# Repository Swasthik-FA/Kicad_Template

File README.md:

<!--PCB_BLOCK-->
<table align="center">
  <tr>
    <td align="center">
      
      <br><sub><b>Front</b></sub>
    </td>
    <td align="center">
      
      <br><sub><b>Back</b></sub>
    </td>
  </tr>
</table>

***

## SPECIFICATIONS

| Parameter | Value |
| --- | --- |
| Dimensions | 125.74 x 53.08 mm |
<!--/PCB_BLOCK-->

***

## DIRECTORY STRUCTURE

    .
    ├─ .github/workflows  # CI pipeline (feature push, PR gates, release)
    ├─ HTML               # Generated reports / Pages site (CI output)
    ├─ config             # KiBot YAML configs and report templates
    │  ├─ kibot           # Orchestrator + per-output YAMLs
    │  └─ web             # Themed CSS for generated HTML
    ├─ docs               # Project images and documentation assets
    ├─ hardware           # KiCad project (source of truth)
    ├─ manufacturing      # Auto-generated fabrication artifacts
    └─ scripts            # Helper scripts (rename project)

<h1 align="center"><!--REPO_NAME-->Kicad_Template<!--/REPO_NAME--></h1>

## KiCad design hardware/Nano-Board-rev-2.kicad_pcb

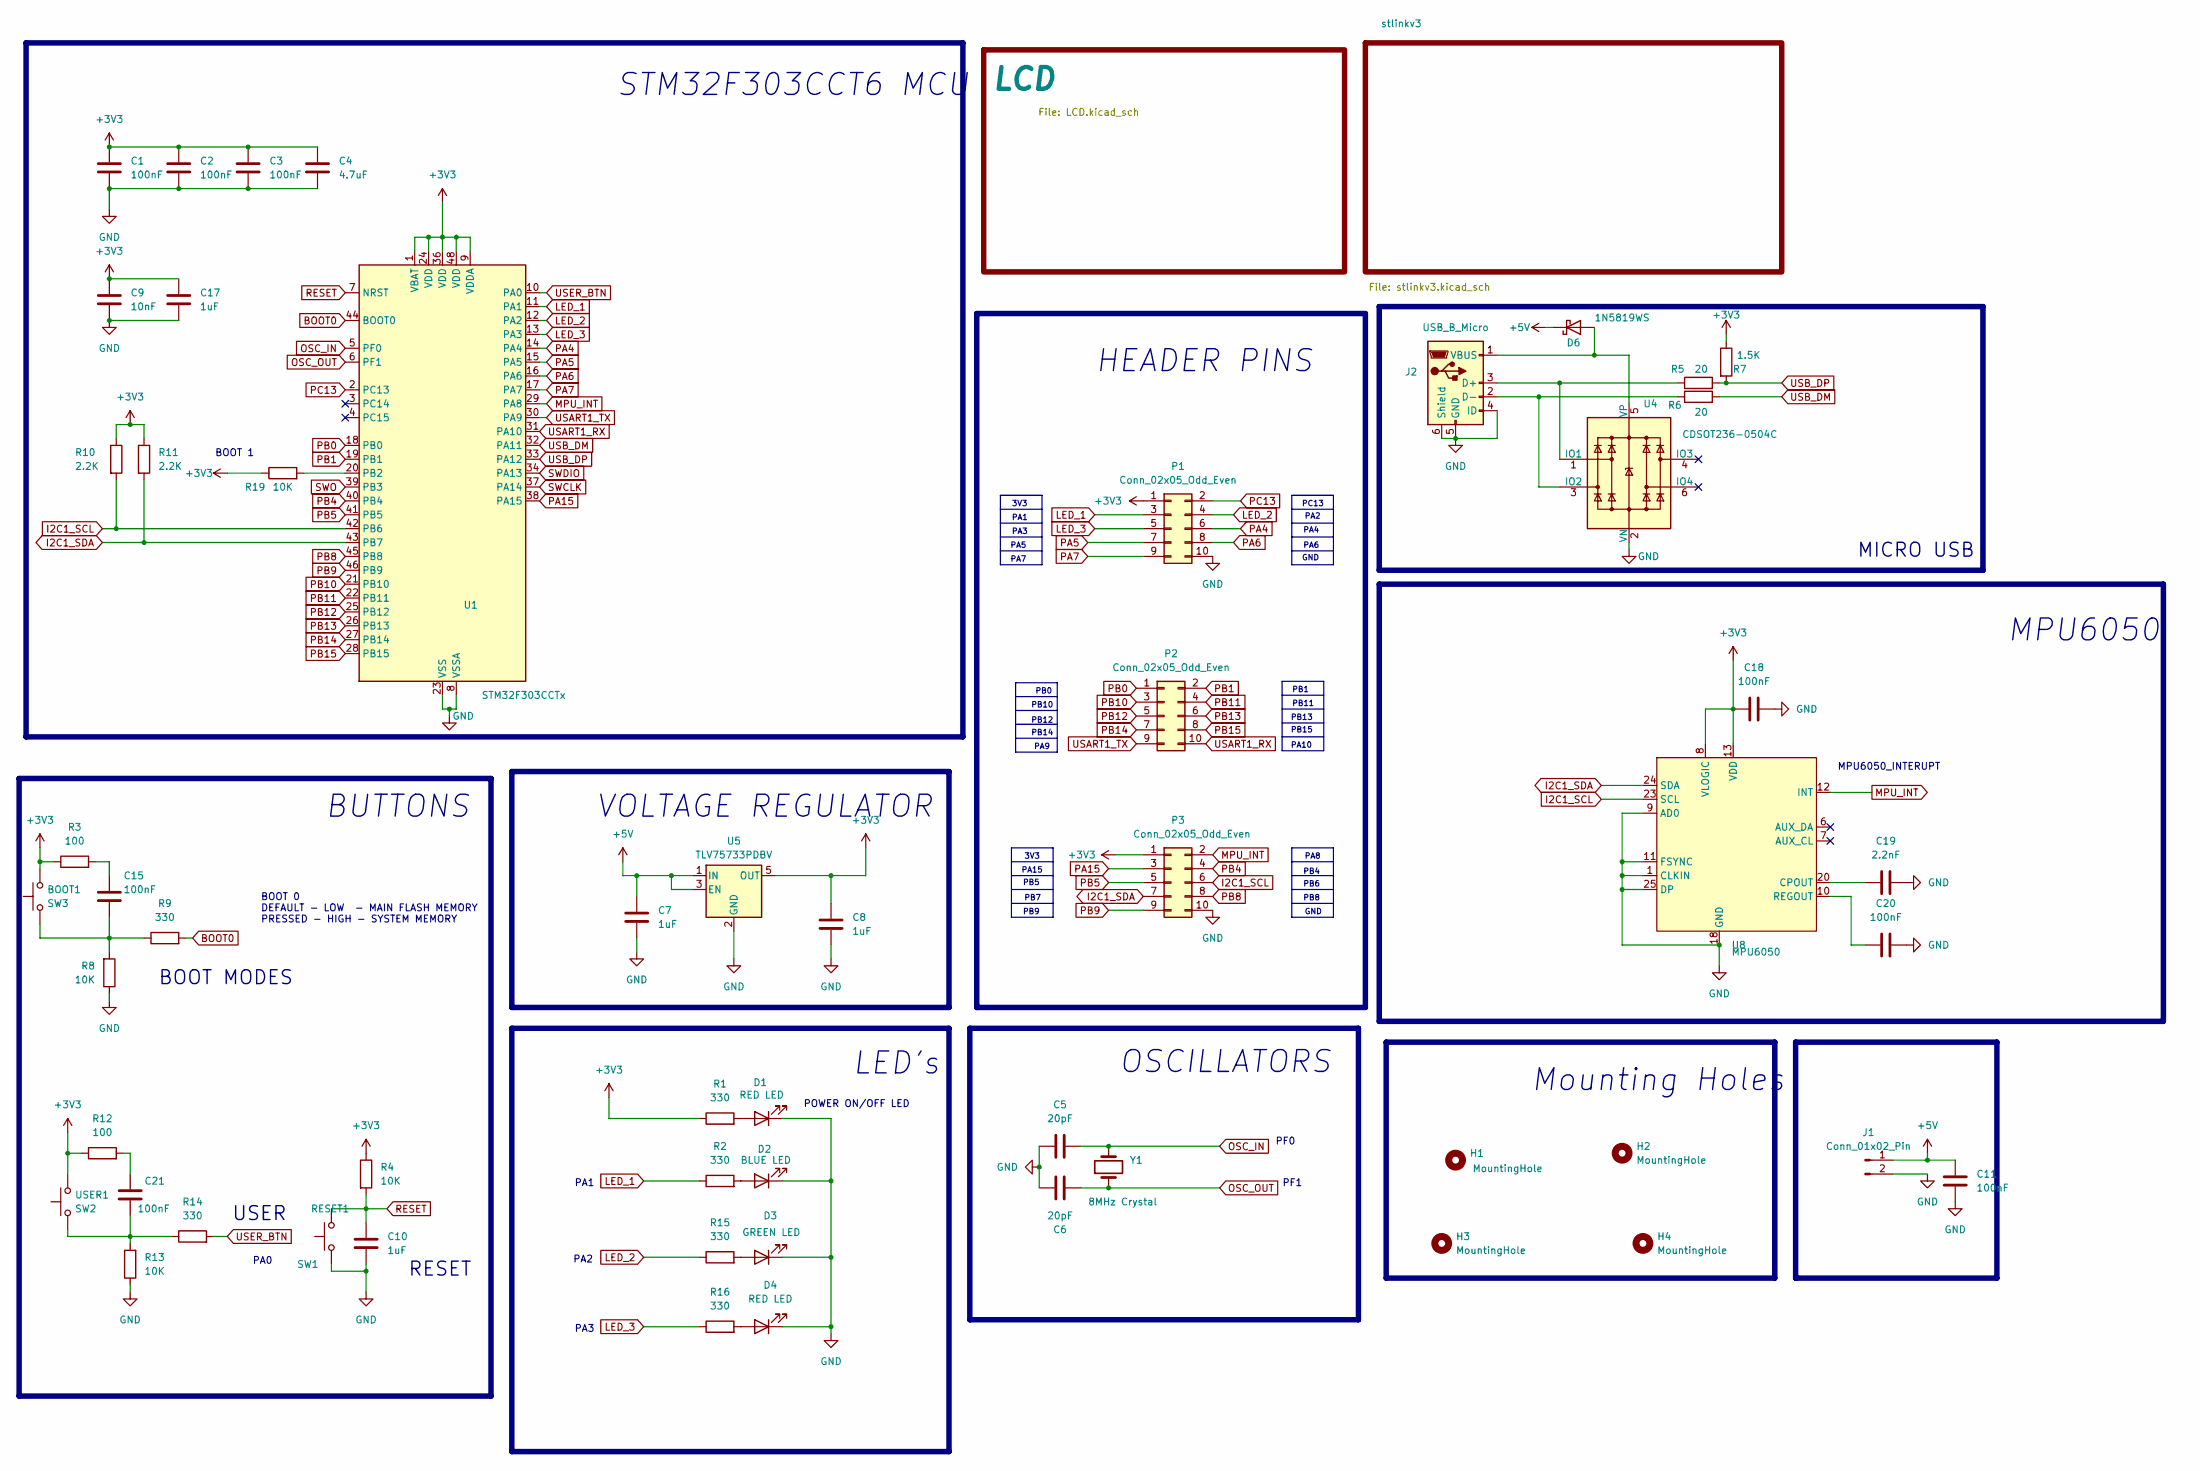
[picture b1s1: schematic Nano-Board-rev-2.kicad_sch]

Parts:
BOOT1: SW3; SW_Tactile_SPST_NO_Straight_CK_PTS636Sx25SMTRLFS; MPN TS1101-C-W; LCSC C318938
C1, C2, C3, C15, C18, C20, C21: 100nF; C_0402_1005Metric; MPN TCC0402X5R1 04Z160A; LCSC C48579247
C4: 4.7uF; C_0402_1005Metric; MPN TCC0402X5R4 75M6R3AT; LCSC C48579247
C5, C6: 20pF; C_0402_1005Metric; MPN 0402CG200J50 0NT; LCSC C1554
C7, C8: 1uF; C_0402_1005Metric; LCSC C7503519
C9: 10nF; C_0402_1005Metric; MPN CC0402KRX7R9BB; LCSC C60133
C10, C17: 1uF; C_0402_1005Metric; MPN CL05A105KP5NNNC; LCSC C7503519
C11: 100nF; C_0402_1005Metric
C19: 2.2nF; C_0402_1005Metric; MPN 0402B222K500CT; LCSC C338130
D1, D4: RED LED; LED_0603_1608Metric; MPN BLHUB37A-AV-TRB; LCSC C165980
D2: BLUE LED; LED_0603_1608Metric; MPN BLHB337A-AV-TRB; LCSC C165977
D3: GREEN LED; LED_0603_1608Metric; MPN SZYY0402YG; LCSC C434449
D6: 1N5819WS; D_SOD-123; LCSC C191023
H1, H2, H3, H4: MountingHole; MountingHole_2.2mm_M2
J1: Conn_01x02_Pin; PinSocket_1x02_P2.54mm_Vertical
J2: USB_B_Micro; micro_USB; MPN KH2.54FH1X12P-H8.5; LCSC C25503144
P1, P2, P3: Conn_02x05_Odd_Even; PinSocket_2x05_P2.54mm_Vertical_SMD; MPN 2.54-2*5P; LCSC C843271
R1, R2, R9, R14, R15, R16: 330; R_0402_1005Metric; MPN FRC0402J331 TS; LCSC C2906929
R3, R12: 100; R_0402_1005Metric; MPN SCR0402J100R; LCSC C3017466
R4: 10K; R_0402_1005Metric; MPN SCR0402J100K; LCSC C51035904
R5, R6: 20; R_0402_1005Metric; MPN RC0402FR-0720RL; LCSC C138031
R7: 1.5K; R_0402_1005Metric; MPN FRC0402J152TS; LCSC C2929900
R8, R13, R19: 10K; R_0402_1005Metric; MPN SCR0402F10K; LCSC C51035904
R10, R11: 2.2K; R_0402_1005Metric; MPN CR0402FF2201G; LCSC C100309
RESET1: SW1; SW_Tactile_SPST_NO_Straight_CK_PTS636Sx25SMTRLFS; MPN TS1101-C-W; LCSC C318938
U1: STM32F303CCTx; LQFP-48_7x7mm_P0.5mm; MPN STM32F303CC T6; LCSC C81523
U4: CDSOT236-0504C; SOT-23-6; MPN CDSOT236- 0504C; LCSC C41409337
U5: TLV75733PDBV; SOT-23-5; LCSC C485517
U8: MPU6050; Mpu6050; MPN MPU-6050
USER1: SW2; SW_Tactile_SPST_NO_Straight_CK_PTS636Sx25SMTRLFS; MPN TS1101-C-W; LCSC C318938
Y1: 8MHz Crystal; Crystal_SMD_HC49-SD; MPN X49SM8MSD2; LCSC C12674

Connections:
+3V3: BOOT1.2, C1.1, C2.1, C3.1, C4.1, C8.1, C9.1, C17.1, C18.1, P1.1, P3.1, R1.1, R3.1, R4.1, R7.1, R10.1, R11.1, R12.1, R19.1, U1.1 (VBAT), U1.9 (VDDA), U1.24 (VDD), U1.36 (VDD), U1.48 (VDD), U5.5 (OUT), U8.8 (VLOGIC), U8.13 (VDD), USER1.2; also elsewhere on the board
+5V: C7.1, C11.1, D6.1 (K), J1.1, U5.1 (IN), U5.3 (EN); also elsewhere on the board
BOOT0: R9.2, U1.44 (BOOT0)
GND: C1.2, C2.2, C3.2, C4.2, C5.1, C6.1, C7.2, C8.2, C9.2, C10.2, C11.2, C17.2, C18.2, C19.2, C20.2, D1.1 (K), D2.1 (K), D3.1 (K), D4.1 (K), J1.2, J2.4 (ID), J2.5 (GND), J2.6 (Shield), P1.10, P3.10, R8.1, R13.1, RESET1.1, U1.8 (VSSA), U1.23 (VSS), U1.35 (VSS), U1.47 (VSS), U4.2 (VN), U5.2 (GND), U8.1 (CLKIN), U8.9 (AD0), U8.11 (FSYNC), U8.18 (GND), U8.25 (DP); also elsewhere on the board
I2C1_SCL: P3.6, R10.2, U1.42 (PB6), U8.23 (SCL)
I2C1_SDA: P3.7, R11.2, U1.43 (PB7), U8.24 (SDA)
LED_1: P1.3, R2.1, U1.11 (PA1)
LED_2: P1.4, R15.1, U1.12 (PA2)
LED_3: P1.5, R16.1, U1.13 (PA3)
MPU_INT: P3.2, U1.29 (PA8), U8.12 (INT)
unnamed 18: BOOT1.1, C15.2, R8.2, R9.1; also elsewhere on the board
unnamed: C15.1, R3.2
unnamed: C21.1, R12.2
unnamed 21: C21.2, R13.2, R14.1, USER1.1; also elsewhere on the board
unnamed: D1.2 (A), R1.2
unnamed: D2.2 (A), R2.2
unnamed: D3.2 (A), R15.2
unnamed: D4.2 (A), R16.2
unnamed: D6.2 (A), J2.1 (VBUS), U4.5 (VP)
unnamed: J2.3 (D+), R5.1, U4.1 (IO1)
unnamed: J2.2 (D-), R6.1, U4.3 (IO2)
unnamed: R19.2, U1.20 (PB2)
unnamed: C19.1, U8.20 (CPOUT)
unnamed: C20.1, U8.10 (REGOUT)
OSC_IN: C5.2, U1.5 (PF0), Y1.2
OSC_OUT: C6.2, U1.6 (PF1), Y1.1
PA4: P1.6, U1.14 (PA4)
PA5: P1.7, U1.15 (PA5)
PA6: P1.8, U1.16 (PA6)
PA7: P1.9, U1.17 (PA7)
PA15: P3.3, U1.38 (PA15)
PB0: P2.1, U1.18 (PB0)
PB1: P2.2, U1.19 (PB1)
PB4: P3.4, U1.40 (PB4)
PB5: P3.5, U1.41 (PB5)
PB8: P3.8, U1.45 (PB8)
PB9: P3.9, U1.46 (PB9)
PB10: P2.3, U1.21 (PB10)
PB11: P2.4, U1.22 (PB11)
PB12: P2.5, U1.25 (PB12)
PB13: P2.6, U1.26 (PB13)
PB14: P2.7, U1.27 (PB14)
PB15: P2.8, U1.28 (PB15)
PC13: P1.2, U1.2 (PC13)
RESET: C10.1, R4.2, RESET1.2, U1.7 (NRST); also elsewhere on the board
SWCLK: U1.37 (PA14); also elsewhere on the board
SWDIO: U1.34 (PA13); also elsewhere on the board
SWO: U1.39 (PB3); also elsewhere on the board
USART1_RX: P2.10, U1.31 (PA10); also elsewhere on the board
USART1_TX: P2.9, U1.30 (PA9); also elsewhere on the board
USB_DM: R6.2, U1.32 (PA11)
USB_DP: R5.2, R7.2, U1.33 (PA12)
USER_BTN: R14.2, U1.10 (PA0)

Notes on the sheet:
PB11
PB12
PF0
PB7
PA10
PB6
PC13
STM32F303CCT6 MCU
POWER ON/OFF LED
PA1
3V3
RESET
Mounting Holes
BUTTONS
BOOT MODES
PB15
PA3
PB9
MICRO USB
PB5
PA7
PB13
BOOT 1
PF1
PB4
VOLTAGE REGULATOR
GND
PA9
MPU6050
MPU6050_INTERUPT
PA2
PA15
PB0
PA8
LED's
PB14
PB8
USER
PA4
PB1

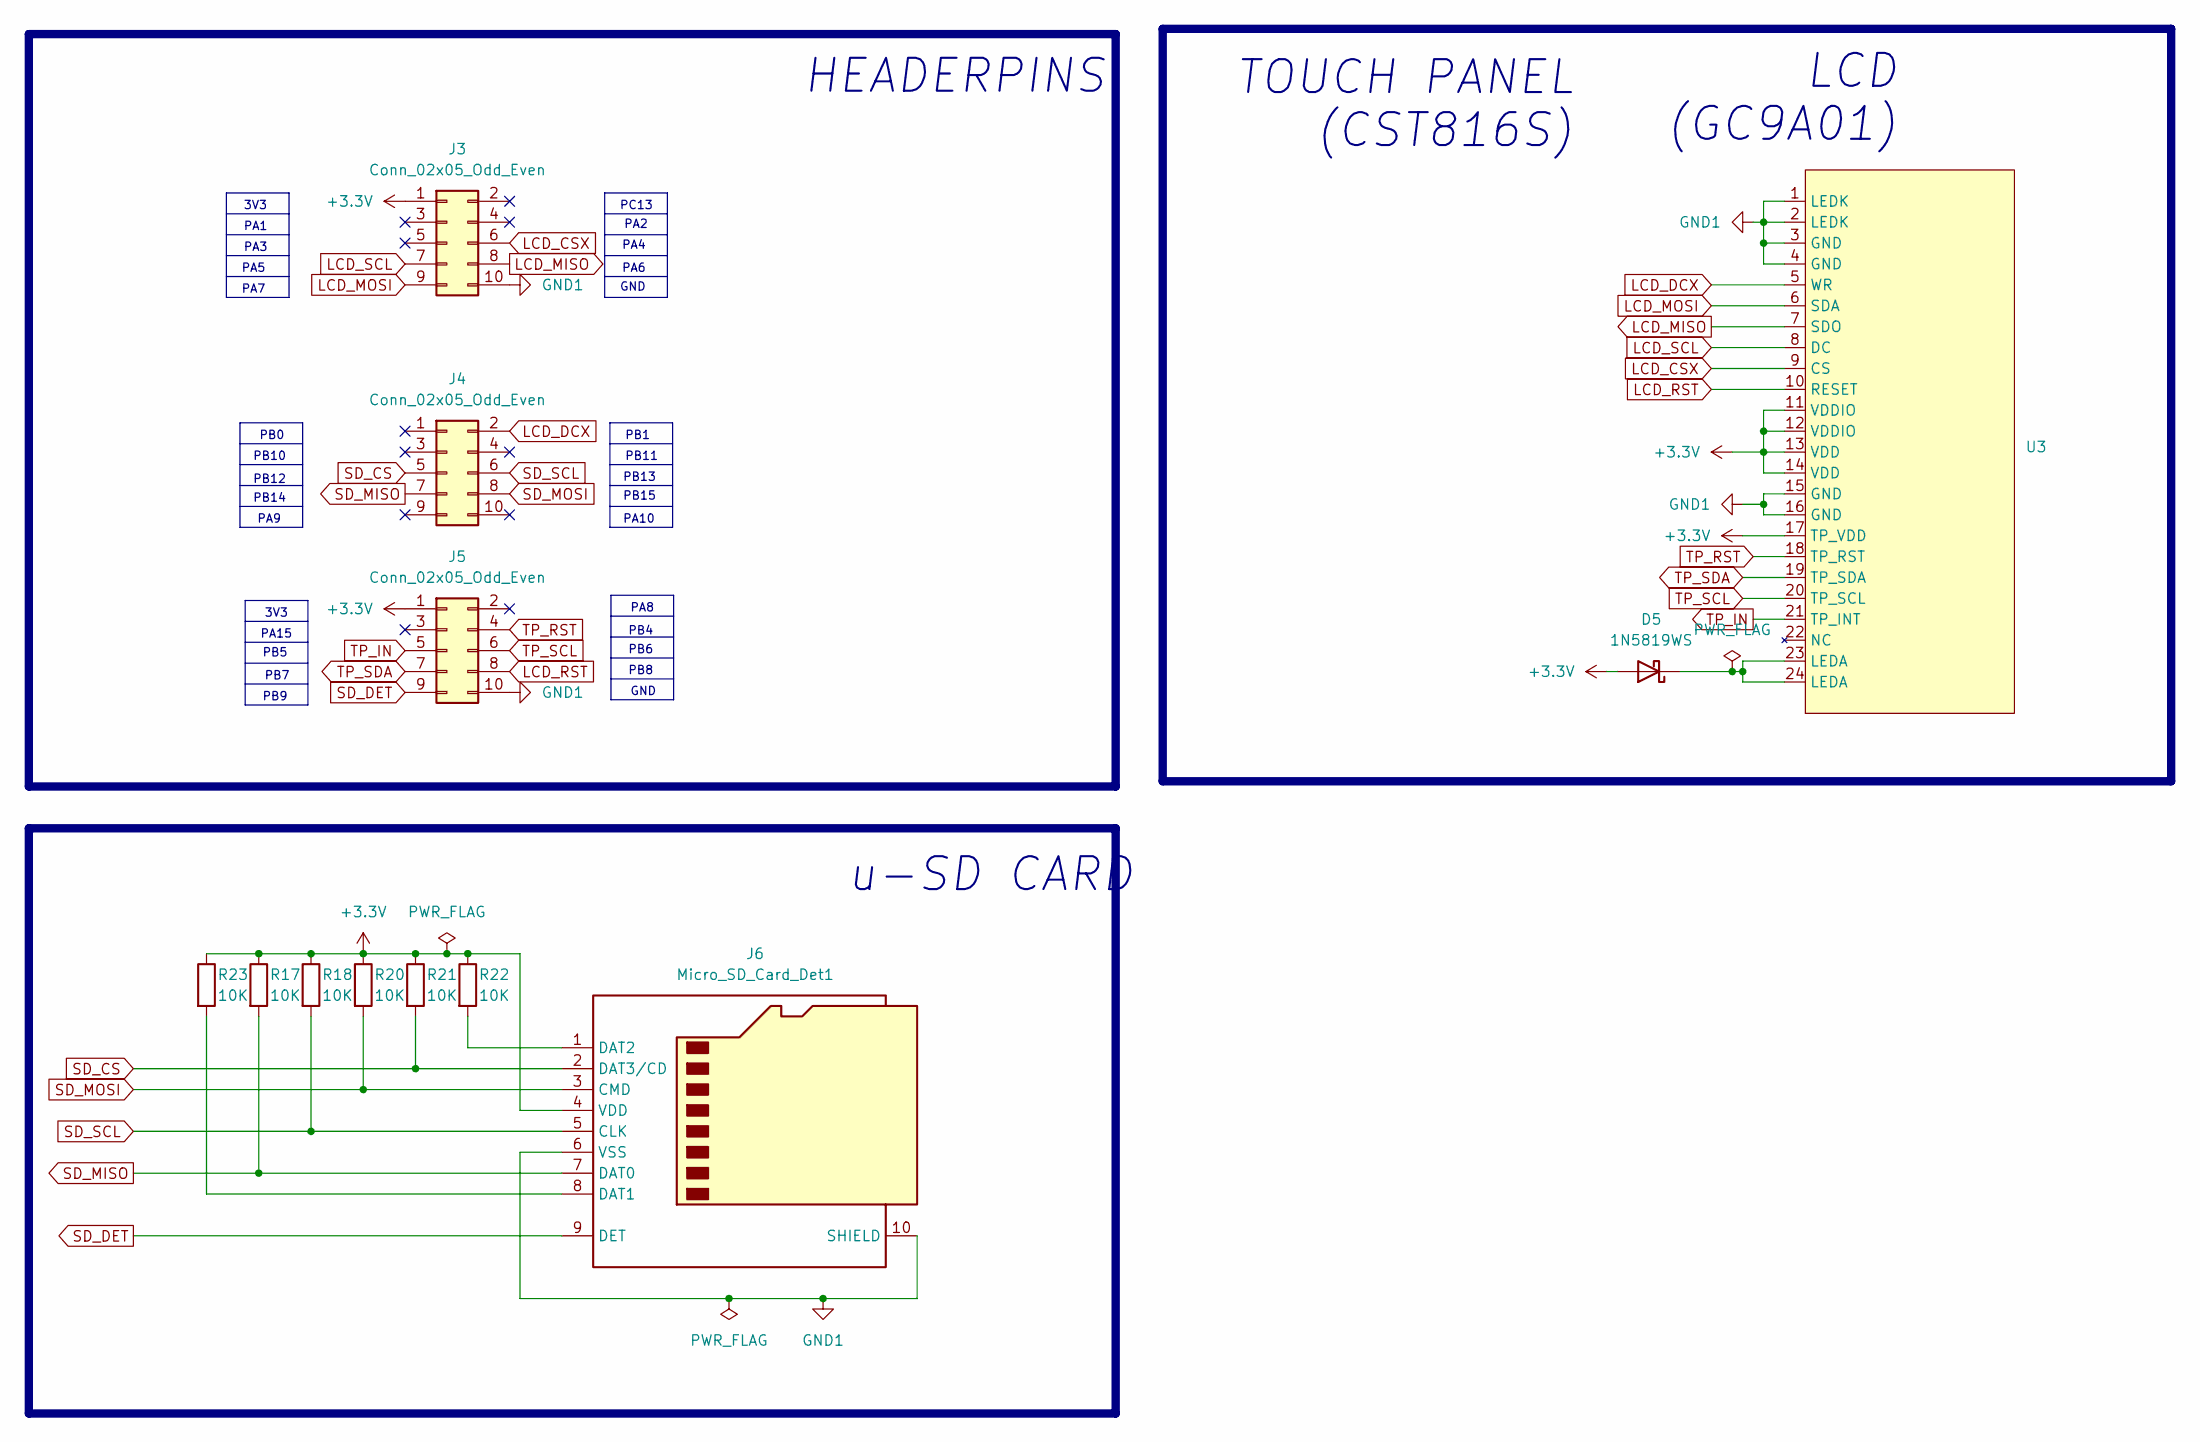
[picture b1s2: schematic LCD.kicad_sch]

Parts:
D5: 1N5819WS; D_SOD-123; LCSC C191023
J3, J4, J5: Conn_02x05_Odd_Even; PinHeader_2x05_P2.54mm_Vertical_SMD; MPN PZ254-2-05-S; LCSC C3294463
J6: Micro_SD_Card_Det1; CUI_MSD-1-A; MPN MLD-TF PUSH-H18; LCSC C52750848
R17, R18, R20, R21, R22, R23: 10K; R_0402_1005Metric; MPN SCR0402F10K; LCSC C51035904
U3: OK-24F024-04

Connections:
+3.3V: D5.2 (A), J3.1, J5.1, J6.4 (VDD), R17.1, R18.1, R20.1, R21.1, R22.1, R23.1, U3.11 (VDDIO), U3.12 (VDDIO), U3.13 (VDD), U3.14 (VDD), U3.17 (TP_VDD)
GND1: J3.10, J5.10, J6.6 (VSS), J6.10 (SHIELD), U3.1 (LEDK), U3.2 (LEDK), U3.3 (GND), U3.4 (GND), U3.15 (GND), U3.16 (GND)
LCD_CSX: J3.6, U3.9 (CS)
LCD_DCX: J4.2, U3.5 (WR)
LCD_MISO: J3.8, U3.7 (SDO)
LCD_MOSI: J3.9, U3.6 (SDA)
LCD_RST: J5.8, U3.10 (RESET)
LCD_SCL: J3.7, U3.8 (DC)
unnamed: D5.1 (K), U3.23 (LEDA), U3.24 (LEDA)
unnamed: J6.8 (DAT1), R23.2
unnamed: J6.1 (DAT2), R22.2
SD_CS: J4.5, J6.2 (DAT3/CD), R21.2
SD_DET: J5.9, J6.9 (DET)
SD_MISO: J4.7, J6.7 (DAT0), R17.2
SD_MOSI: J4.8, J6.3 (CMD), R20.2
SD_SCL: J4.6, J6.5 (CLK), R18.2
TP_IN: J5.5, U3.21 (TP_INT)
TP_RST: J5.4, U3.18 (TP_RST)
TP_SCL: J5.6, U3.20 (TP_SCL)
TP_SDA: J5.7, U3.19 (TP_SDA)

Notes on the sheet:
TOUCH PANEL (CST816S)
PA4
PB15
PB11
PB14
PA5
PA2
u-SD CARD
PA3
LCD (GC9A01)
PB7
PA1
PA10
PA6
PB12
GND
PB9
PB4
3V3
PB1
PB8
PA8
PA7
PC13
PA9
PB6
PB13
HEADERPINS
PB0
PB10
PB5
PA15

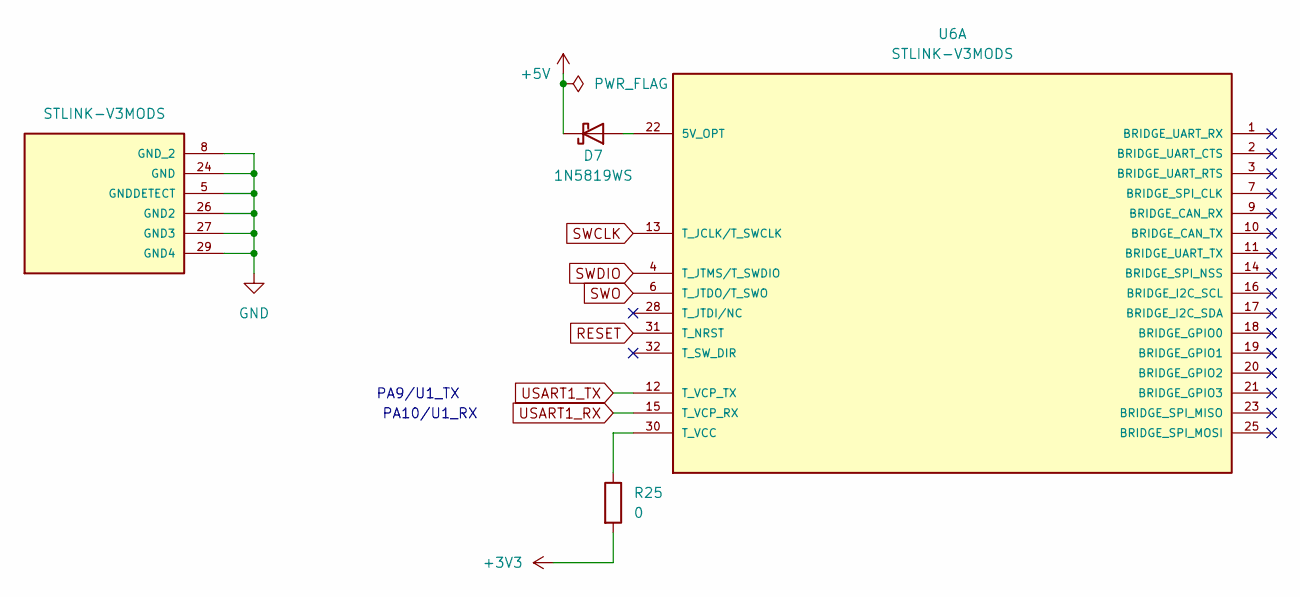
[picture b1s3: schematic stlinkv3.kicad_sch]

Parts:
D7: 1N5819WS; D_SOD-123; LCSC C191023
R25: 0; R_0603_1608Metric
U6: STLINK-V3MODS; MODULE_STLINK-V3MODS; PARTREV 1

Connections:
+3V3: R25.2; also elsewhere on the board
+5V: D7.1 (K); also elsewhere on the board
GND: U6.5 (GNDDETECT), U6.8 (GND_2), U6.24 (GND), U6.26 (GND2), U6.27 (GND3), U6.29 (GND4); also elsewhere on the board
unnamed: D7.2 (A), U6.22 (5V_OPT)
unnamed: R25.1, U6.30 (T_VCC)
RESET: U6.31 (T_NRST); also elsewhere on the board
SWCLK: U6.13 (T_JCLK/T_SWCLK); also elsewhere on the board
SWDIO: U6.4 (T_JTMS/T_SWDIO); also elsewhere on the board
SWO: U6.6 (T_JTDO/T_SWO); also elsewhere on the board
USART1_RX: U6.15 (T_VCP_RX); also elsewhere on the board
USART1_TX: U6.12 (T_VCP_TX); also elsewhere on the board

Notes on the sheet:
PA9/U1_TX
PA10/U1_RX

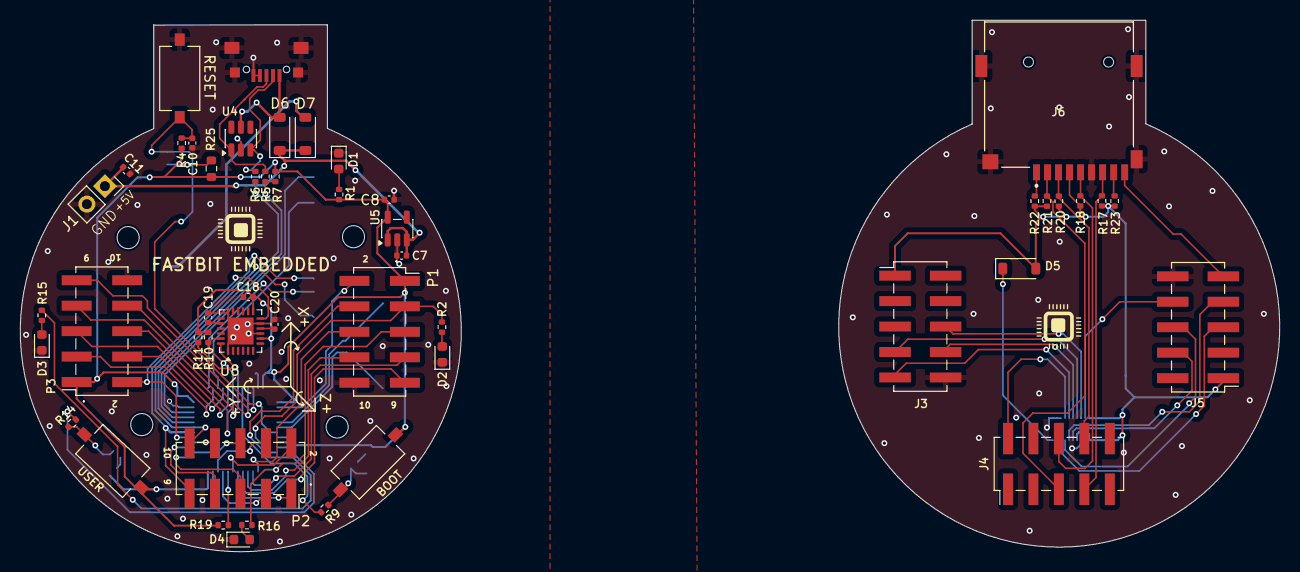
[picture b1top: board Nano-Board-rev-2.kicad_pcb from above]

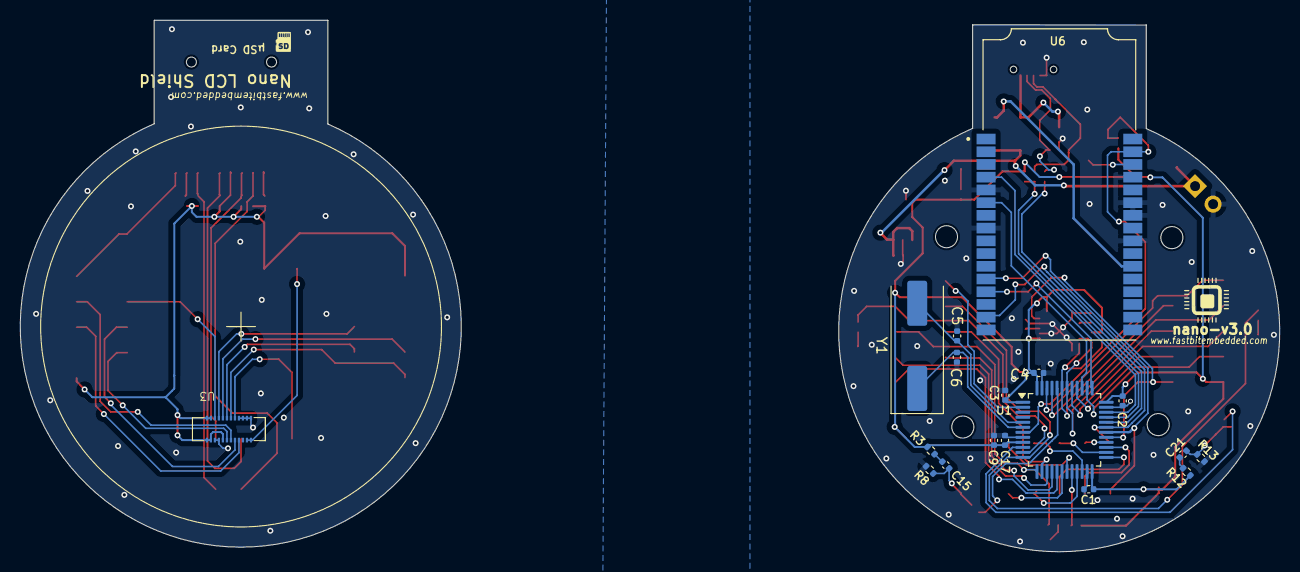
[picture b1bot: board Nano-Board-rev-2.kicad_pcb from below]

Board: 2 copper layers, 44.0 x 52.6 mm, 71 parts (18 on the bottom side), 75 nets.

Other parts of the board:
BOOT: SW3; SW_Tactile_SPST_NO_Straight_CK_PTS636Sx25SMTRLFS
RESET: SW1; SW_Tactile_SPST_NO_Straight_CK_PTS636Sx25SMTRLFS
USER: SW2; SW_Tactile_SPST_NO_Straight_CK_PTS636Sx25SMTRLFS

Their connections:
+3V3: BOOT.2, USER.2; also elsewhere on the board
GND: RESET.1; also elsewhere on the board
unnamed 18: BOOT.1; also elsewhere on the board
unnamed 21: USER.1; also elsewhere on the board
RESET: RESET.2; also elsewhere on the board

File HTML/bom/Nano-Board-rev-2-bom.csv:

Reference,Value,Footprint,Quantity,LCSC Part #,MPN,Manufacturer
BOOT1,SW3,SW_Tactile_SPST_NO_Straight_CK_PTS636Sx25SMTRLFS,1,C318938,TS1101-C-W,C318936 TS1101-C-W
C5 C6,20pF,C_0402_1005Metric,2,C1554,0402CG200J50 0NT,FH (Guangdong Fenghua Advanced Tech 0402CG200J500NT
C19,2.2nF,C_0402_1005Metric,1,C338130,0402B222K500CT,Walsin Tech Corp 0402B222K500CT
C9,10nF,C_0402_1005Metric,1,C60133,CC0402KRX7R9BB,YAGEO CC0402KRX7R9BB103
C1 C2 C3 C11 C15 C18 C20 C21,100nF,C_0402_1005Metric,8,C48579247,TCC0402X5R1 04Z160A,CCTC 0402X7R104K160NT
C7 C8 C10 C17,1uF,C_0402_1005Metric,4,C7503519,CL05A105KP5NNNC,CGA0402X5R105K6R3GT Samsung
C4,4.7uF,C_0402_1005Metric,1,C48579247,TCC0402X5R4 75M6R3AT,CCTC 0402X7R104K160NT
D5 D6 D7,1N5819WS,D_SOD-123,3,C191023,,1N5819WS
D2,BLUE LED,LED_0603_1608Metric,1,C165977,BLHB337A-AV-TRB,BrtLed(Bright LED Elec) BL-HB337A-AV-TRB
D3,GREEN LED,LED_0603_1608Metric,1,C434449,SZYY0402YG,Yongyu Photoelectric SZYY0402YG
D1 D4,RED LED,LED_0603_1608Metric,2,C165980,BLHUB37A-AV-TRB,BrtLed(Bright LED Elec) BL-HUB37A-AV-TRB
J1,Conn_01x02_Pin,PinSocket_1x02_P2.54mm_Vertical,1,,,
J3 J4 J5,Conn_02x05_Odd_Even,PinHeader_2x05_P2.54mm_Vertical_SMD,3,C3294463,PZ254-2-05-S,HCTL PZ254-2-05-S
J6,Micro_SD_Card_Det1,CUI_MSD-1-A,1,C52750848,MLD-TF PUSH-H18,MLD-TF PUSH-H18
J2,USB_B_Micro,micro_USB,1,C25503144,KH2.54FH1X12P-H8.5,HCTL 051T-4BH89-S
P1 P2 P3,Conn_02x05_Odd_Even,PinSocket_2x05_P2.54mm_Vertical_SMD,3,C843271,2.54-2*5P,Liansheng 2.54-2*5P
R25,0,R_0603_1608Metric,1,,,
R5 R6,20,R_0402_1005Metric,2,C138031,RC0402FR-0720RL,YAGEO RC0402FR-0720RL
R3 R12,100,R_0402_1005Metric,2,C3017466,SCR0402J100R,VO SCR0402J100R
R1 R2 R9 R14 R15 R16,330,R_0402_1005Metric,6,C2906929,FRC0402J331 TS,FOJAN FRC0402J331 TS
R7,1.5K,R_0402_1005Metric,1,C2929900,FRC0402J152TS,FOJAN FRC0402J152TS
R10 R11,2.2K,R_0402_1005Metric,2,C100309,CR0402FF2201G,LIZ Elec CR0402FF2201G
R8 R13 R17 R18 R19 R20 R21 R22 R23,10K,R_0402_1005Metric,9,C51035904,SCR0402F10K,VO CL0402JN10KP
R4,10K,R_0402_1005Metric,1,C51035904,SCR0402J100K,VO CL0402JN10KP
RESET1,SW1,SW_Tactile_SPST_NO_Straight_CK_PTS636Sx25SMTRLFS,1,C318938,TS1101-C-W,C318936 TS1101-C-W
U4,CDSOT236-0504C,SOT-23-6,1,C41409337,CDSOT236- 0504C,Leiditech CDSOT236-0504C-ES
U8,MPU6050,Mpu6050,1,,MPU-6050,InvenSense MPU-6050
U6,STLINK-V3MODS,MODULE_STLINK-V3MODS,1,,,ST Microelectronics
U1,STM32F303CCTx,LQFP-48_7x7mm_P0.5mm,1,C81523,STM32F303CC T6,STMicroelectro nics STM32F303CC T6
U5,TLV75733PDBV,SOT-23-5,1,C485517,,TLV75733PDBVR
U3,~,OK-24F024-04,1,,,
USER1,SW2,SW_Tactile_SPST_NO_Straight_CK_PTS636Sx25SMTRLFS,1,C318938,TS1101-C-W,C318936 TS1101-C-W
Y1,8MHz Crystal,Crystal_SMD_HC49-SD,1,C12674,X49SM8MSD2,YXC X49SM8MSD2SC

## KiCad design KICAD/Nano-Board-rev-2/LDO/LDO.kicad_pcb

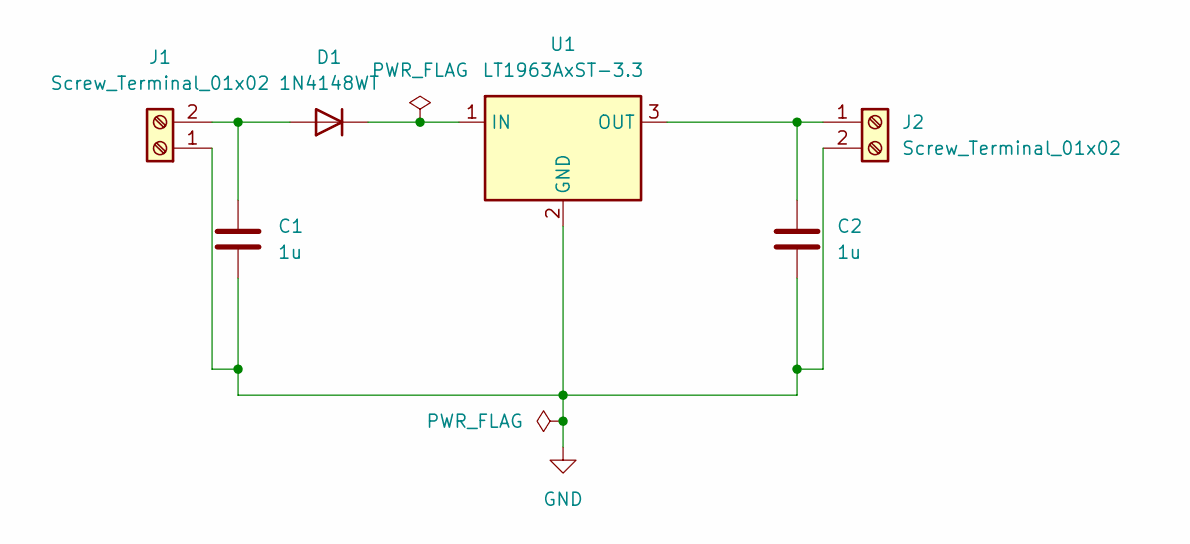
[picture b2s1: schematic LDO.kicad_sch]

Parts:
C1, C2: 1u; C_0805_2012Metric
D1: 1N4148WT; D_SOD-523
J1, J2: Screw_Terminal_01x02; TerminalBlock_MaiXu_MX126-5.0-02P_1x02_P5.00mm
U1: LT1963AxST-3.3; SOT-223-3_TabPin2

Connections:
GND: C1.2, C2.2, J1.1, J2.2, U1.2 (GND)
unnamed: C1.1, D1.2 (A), J1.2
unnamed: D1.1 (K), U1.1 (IN)
unnamed: C2.1, J2.1, U1.3 (OUT)

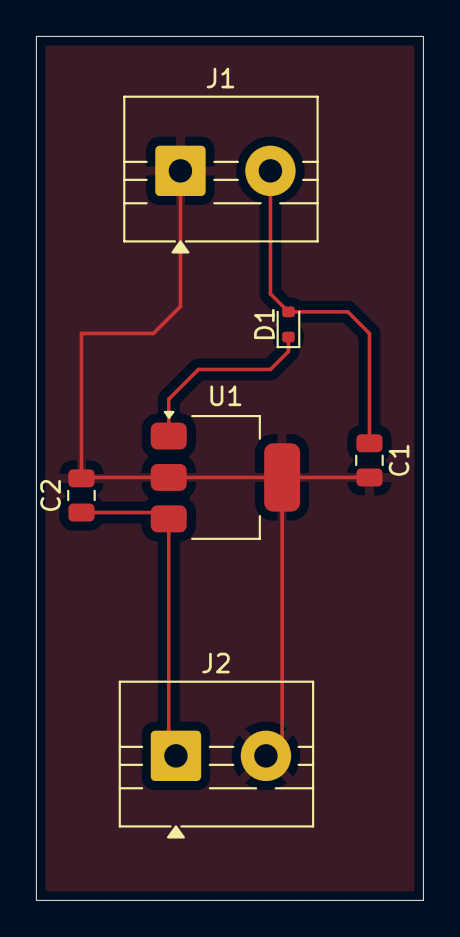
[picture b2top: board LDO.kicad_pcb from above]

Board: 2 copper layers, 21.5 x 48.0 mm, 6 parts (0 on the bottom side), 4 nets.

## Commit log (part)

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2026-05-02 trigger pipeline
2026-05-02 Remove deprecated KiBot preflight option, fix gitignore
    - Drop ignore_unconnected from preflight blocks in both KiBot configs;
    it triggered W143 deprecation warnings in CI.
    - Escape the leading # in the auto-save gitignore entry so it actually
    ignores the file instead of being read as a comment.
    - Untrack KiCad auto-save marker that should not have been committed.
2026-05-02 Replace flaky SVG schematic export with PDF + 3D PNG renders
    Modeled on the Fastbit reference KiBot project.
    - Drop svg_sch_print from the visual preset. kicad-cli sch export svg
    returns exit 3 with no diagnostics on projects that reference local
    symbol libraries (the reference project avoids this output type for
    the same reason).
    - Keep pdf_sch_print as the schematic preview — same backend, more
2026-05-02 Drop schematic PDF from visual preset (kicad-cli sch export broken)
    kicad-cli sch export pdf returns exit 3 on this project's .kicad_sch,
    the same way sch export svg did. The format is not the issue —
    something in the schematic file itself is rejected by kicad-cli's
    loader. Until that is diagnosed, KiBot's first-error-stops-everything
    behaviour means the schematic output blocks every render that comes
    after it.
2026-05-04 ci: refresh 3D PCB renders for README [skip ci]
2026-05-04 Use flat top/bottom 3D renders in README
    Switch the two README hero images from the angled-isometric variants to
    the straight top/bottom views, which read more clearly at thumbnail
    size on the GitHub repo page.
2026-05-04 fix(kibot): use proper isometric rotation steps for 3D angled renders
    KiBot's render_3d rotate_x/y/z and zoom are integer step counts, not
    degrees. Previous values (30/0/20) over-rotated past a usable angle.
    Adopt the reference Fastbit project's tuned values:
    ROTATE_X: 2, ROTATE_Y: -1, ROTATE_Z: ±1, ZOOM: -1
    Z is negated for the bottom view to mirror the top isometric.
2026-05-04 Use repo logo and name in README header
    - Replace placeholder Logos/dummy_logo.svg with docs/Kicad_Template.png
    - Set H1 title to the repo name (Kicad_Template)
2026-05-04 Remove design/ folder; move renders to top-level Images/
    - Delete design/pcb/outputs/ tree (HTML site already lives in HTML/)
    - Move 4 PNG renders to Images/ at the repo root
    - Update workflow DEST and README image paths to Images/
2026-05-04 Drop logo and title; keep CI badge at bottom
2026-05-04 Restore README ordering: header → renders → specs → tree
    Move logo, title, and CI badge back to the top, add the missing
    horizontal rule between the front/back render table and the
    Specifications section, and drop the trailing stray rule.
2026-05-04 Restructure README hero: angled board render above title
    - Drop the broken Images/dummy_image.png placeholder
    - Move the angled-top render in as a wide hero image directly under the
    logo
    - Keep the board name (H1) and CI badge underneath the hero so the page
    reads logo → board → name → badge → front/back renders
2026-05-04 Make ERC/DRC navigate links resolve
    Two fixes so the navigate webpage's report buttons open something:
    1. kicad-cli rejected '-f json'. KiCad 9 expects '--format json', so
    the erc.json / drc.json files were never created.
    2. The navigate_results page links to erc-erc.{html,rpt,json} and
    drc-drc.{html,rpt,json}, but KiBot's preflights don't reliably
    produce those filenames in this image. Alias the kicad-cli outputs
2026-05-04 Revert "Force navigate report links to download .rpt/.json/..."
    This reverts commit 8096510da912ece5102c8424ad9ebb6de3c49b1a.
2026-05-04 Force navigate report links to download .rpt/.json/...
    - Make alias step explicit and overwrite-safe; log before/after
    contents of output/reports/ so failures are diagnosable
    - After mirroring output/ into HTML/, post-process every navigate_*.html
    page: replace onclick='location.href=URL' with a JS snippet that
    builds a temporary <a download> and clicks it, so clicking links to
    .rpt/.json/.csv/.step/.gbr/.drl/.gbrjob/Gerber files triggers a
2026-05-04 pcb: reroute traces on nets 2 and 68
    - Adjust segment endpoints on net 2 around U-region near (88, 116) for cleaner routing
    - Reroute net 68 traces with intermediate waypoint at (82.7, 115.7) / (88.1, 115.7)
    - No net or footprint changes; routing-only update on F.Cu
2026-05-04 report: hide unrequested kind in single-kind HTML pages
    generate_error_report.py always rendered both ERC and DRC sections (cards,
    status badges, violation tables) even when called with inputs for only one
    kind, so erc-erc.html showed an empty DRC section and drc-drc.html showed
    an empty ERC section.
    A kind is now considered "requested" if at least one of its --<kind>-json
    or --<kind>-rpt flags is passed. The per-kind pages produced by the
2026-05-04 Revert "ci: render interactive 3D PCB model in navigate_3d page"
    This reverts commit 6bd4b405a4367433604713a94b7fdbea887c9e68.
2026-05-04 ci: temporarily trigger Pages deploy on feature/test-pipeline
    Lets us verify the deployment end-to-end before merging to dev/main.
    Revert this branch from the trigger list once verified.
2026-05-04 Revert "ci: temporarily trigger Pages deploy on feature/test-pipeline"
    This reverts commit b185df92baf65c335741fb718ba242b2b8324bd2.
2026-05-04 web: add vivid colour to the navigate-page theme
    The previous monochrome restraint felt flat. Pump the colour back in
    without breaking the glass+minimal+dashboard structure:
    - Mesh-gradient background: 5 vivid radial blobs (indigo, sky, pink,
    purple, teal) instead of 3 soft ones, ~2x opacity
    - Section heading text now uses a 3-stop gradient fill (accent ->
    accent-strong -> text), tighter tracking, larger weight
2026-05-04 ci: 3D viewer in navigate_3d page + step file as download button
    Re-add the in-browser 3D viewer:
    - New step exports output/3d/<project>.glb via kicad-cli pcb export glb
    with substituted models, tracks, and zones
    - Publish step injects a <model-viewer> at the top of navigate_3d.html
    (640px, dark gradient background, orbit/zoom/pinch enabled)
    - Poster fallback now explains that file:// will not work and gives
2026-05-04 ci: remove the interactive 3D model from navigate_3d page
    Drop the GLB export step and the <model-viewer> injection. The
    "Download STEP" button conversion stays — that piece works without a
    server.
    Reasoning: the model-viewer needs HTTP(S) to load (ES modules are
    blocked over file://). For a project template that's expected to
    "just work" by double-click, that's a footgun. The cleaner answers
2026-05-04 ci: add interactive 3D viewer to navigate_3d page
    - scripts/convert_to_glb.py: thin Python wrapper around
    `kicad-cli pcb export glb`. Auto-detects the PCB under hardware/
    and writes HTML/3d/<project>.glb. PCB->GLB is one CLI hop in the
    kicad_auto:ki9 image; we don't go via .step because that path
    needs Blender/FreeCAD installed and tends to lose colour/structure.
    - New CI step (after KiBot full group) runs the script and drops the
2026-05-05 ci: 3D Viewer = clean button to dedicated Pages page
    Architecture:
    - New dedicated full-screen viewer at HTML/3d-viewer.html (rendered
    in CI from config/web/3d-viewer.html template; placeholders for
    title and GLB URL filled at publish time). Lives at the Pages root,
    so the URL is https://<owner>.github.io/<repo>/3d-viewer.html.
    - The navigate_3d page no longer embeds <model-viewer> inline. Instead
2026-05-05 Revert "ci: navigate_3d page now shows ONLY the 3D viewer"
    This reverts commit bd1be9ccd194c164b426cf3351766ca48d09edd3.
2026-05-05 Revert "ci: 3d-viewer page = model-viewer only, no chrome"
    This reverts commit 227f5ab146e59d59b30d88b1d9eccef9b8e22734.
2026-05-05 Revert "ci: deploy Pages from feature/test-pipeline (temporary, for verification)"
    This reverts commit ee7090a3dac3973bf94298b29ff1de19c1660ce1.
2026-05-05 ci: retry the auto-commit push on conflict (handles parallel runs)
    The publish step fails with "fetch first" when another commit lands on
    main during the run (manual push or a parallel workflow). The build
    itself is fine — only the final push loses the race.
    Add a 5-attempt loop: on rejection, pull --rebase onto the new tip and
    retry. The auto-commit only touches HTML/ and README.md; rebase uses
    strategy ours so HTML conflicts always pick our freshly regenerated
2026-05-06 Revert "ci: refresh 3D PCB renders and README repo name [skip ci]"
    This reverts commit ecf5e19ccf0893330188d003fb74a35d4af01231.
2026-05-06 Removed the pcb Files
2026-05-06 Revert "ci: support schematic-only projects in feature-push workflow"
    This reverts commit 5d7648416adfecb41536fd25376838f4c48a6221.
2026-05-06 ci: dynamic landing page and prune empty navigate tiles
2026-05-06 ci: bundle gerbers into zip and link as download
2026-05-06 ci+readme: dynamic PCB block with photos + computed dimensions
2026-05-06 ci: trigger Pages deploy after HTML auto-commit
2026-05-06 ci(pr-to-dev): enforce feature/* source and post sticky pass/fail summary
2026-05-06 ci: run feature-push workflow on feature/** branches
2026-05-06 ci(pr-to-dev): drop error-report HTML generation and artifact upload
2026-05-06 viewer: switch to JLCPCB-style light background and lighting
2026-05-06 Revert "viewer: switch to JLCPCB-style light background and lighting"
    This reverts commit f152636c7ee8b7318d32c5af8309c5440309829b.
2026-05-07 feat: add Three.js PCB 3D viewer with auto-deploy via GitHub Pages
    - Add config/web/3d-viewer.html: custom Three.js viewer with OrbitControls,
    GLTFLoader+Meshopt, RoomEnvironment, ACES tonemapping, three-light rig,
    soft shadows; top/bottom/reset/background buttons, loading spinner with
    progress, file:// error fallback, mobile-responsive UI
    - Add scripts/convert_to_glb.py: kicad-cli pcb export glb wrapper
    - feature-push.yml: convert PCB to GLB, compress with gltf-transform
2026-05-09 hardware: update PCB layout
    - Trigger feature-push CI to rebuild GLB with layer-preserving compression
2026-05-09 viewer: restore old 3D viewer (pre-eaecf38 version)
